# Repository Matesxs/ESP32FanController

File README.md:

# ESP32 PWM Fan Controller

## Description
### This project is still in development so lot of things can be untested or not working at all!

```text
ESP32 10 channel pwm fan controller with control over tcp sockets and serial, 
temperature readout from onewire temperature probes (unlimited count, board have 2 ports), 
fan control routine (automatic - 20 points temperature curves with option of multiple 
temperature inputs and one external temperature value set by control interfaces, manual) 
for 10 separated channels with rpm readout from tacho sensor and led strip control routine with 
predefined effects (some of them use the temperature probes to be able to display temperature).
```

## Features

* 10 Channels for PWM fans
  * Automatic or manual fan speed control
  * Automatic control with 20 point curves with option for multi source temperature input for each fan
* 2 Channels for one wire temperature probes
* 2 Channels for RGB adressable led strips
  * Predefined effects and some even reacts to temperature
  * Support for both 5V and 12V warriants
* Integration for Argus Monitor
* Power by molex or barrel jack (selectable by jumper when stepdown is present)

## Todo

- [x] Publish Schematics for board
- [x] Rework fan control
- [ ] Rework led control

## References

[ESP32 Docs](https://docs.espressif.com/projects/esp-idf/en/latest/esp32/) \
[PlatformIO](https://platformio.org) \
[NeoPixelBus](https://github.com/Makuna/NeoPixelBus) \
[Argus Monitor](https://www.argusmonitor.com) \
[Argus Monitor Controller example](https://github.com/openfancontrol/arguscontroller) \
[DallasTemperature](https://github.com/milesburton/Arduino-Temperature-Control-Library) \
[ArduinoJson](https://github.com/bblanchon/ArduinoJson)

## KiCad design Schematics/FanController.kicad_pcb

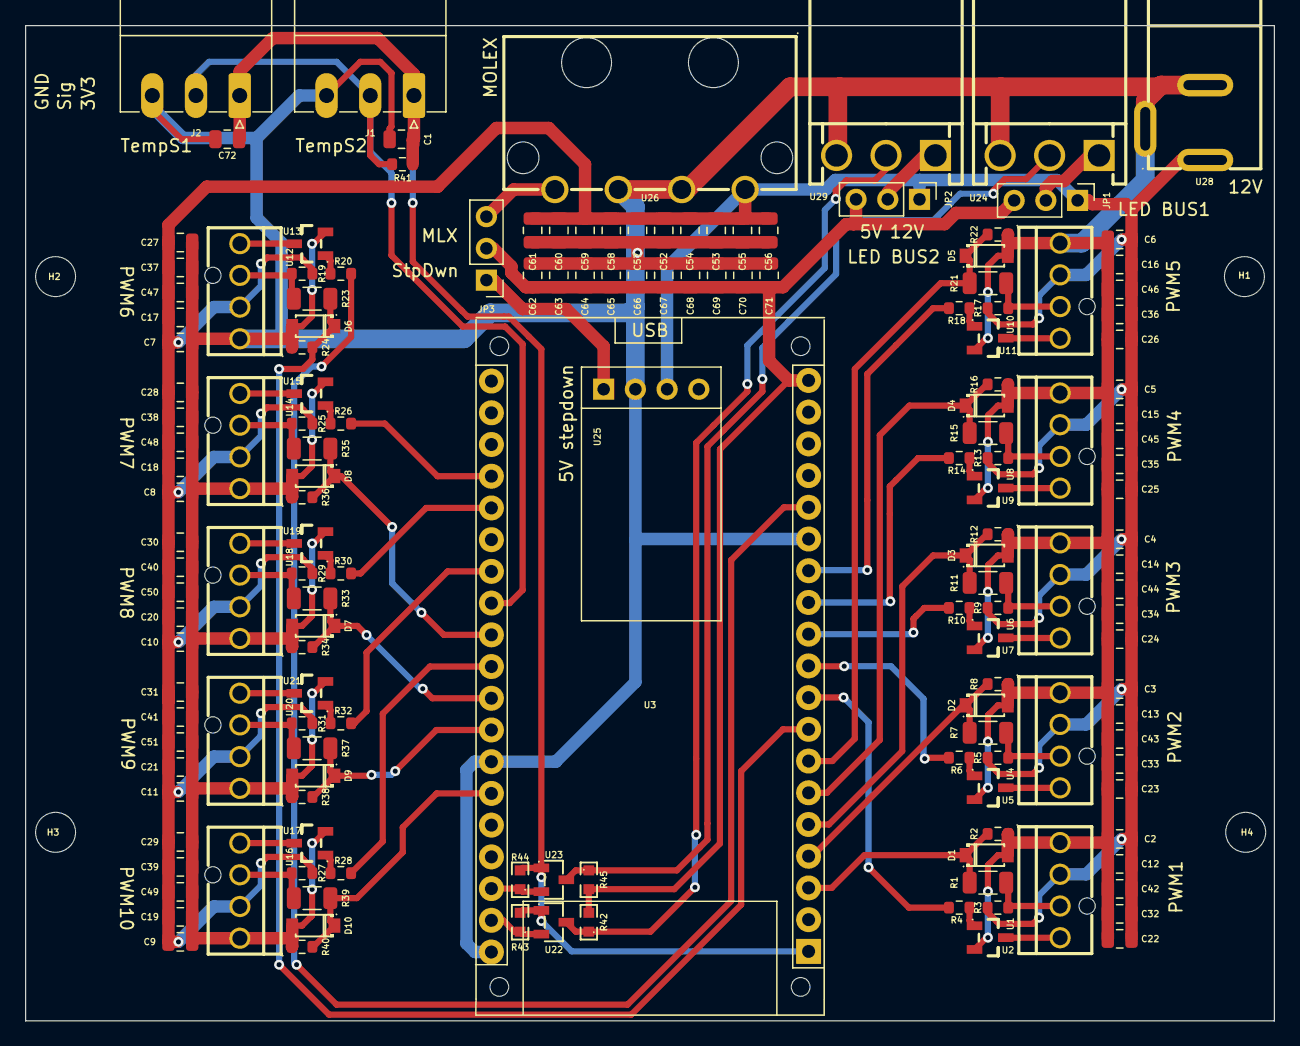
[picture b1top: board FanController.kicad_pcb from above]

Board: 2 copper layers, 100.0 x 79.7 mm, 164 parts (0 on the bottom side), 63 nets.

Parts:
C1, C2, C3, C4, C5, C6, C7, C8, C9, C10, C11, C12, C13, C14, C15, C16, C17, C18, C19, C20, C21, C22, C23, C24, C25, C26, C27, C28, C29, C30, C31, C32, C33, C34, C35, C36, C37, C38, C39, C40, C41, C42, C43, C44, C45, C46, C47, C48, C49, C50, C51, C52, C53, C54, C55, C56, C57, C58, C59, C60, C61, C62, C63, C64, C65, C66, C67, C68, C69, C70, C71, C72: 10u; C_0805_2012Metric
D1, D2, D3, D4, D5, D6, D7, D8, D9, D10: BZT52C3V3; SOD-123_L2.8-W1.8-LS3.7-RD
H1, H2, H3, H4: MountingHole; MountingHole_3.2mm_M3_DIN965
J1: TempSensor1; PhoenixContact_MC_1,5_3-G-3.5_1x03_P3.50mm_Horizontal
J2: TempSensor2; PhoenixContact_MC_1,5_3-G-3.5_1x03_P3.50mm_Horizontal
JP1, JP2: Jumper_3_Open; PinHeader_1x03_P2.54mm_Vertical
JP3: 5V selector; PinHeader_1x03_P2.54mm_Vertical
R1, R7, R11, R15, R21, R23, R33, R35, R37, R39: 2k2; R_1206_3216Metric
R2, R3, R4, R5, R6, R8, R9, R10, R12, R13, R14, R16, R17, R18, R19, R20, R22, R24, R25, R26, R27, R28, R29, R30, R31, R32, R34, R36, R38, R40, R41: 3k3; R_0603_1608Metric
R42, R43, R44, R45: 0603WAF8201T5E; R0603
U1, U4, U6, U8, U10, U12, U14, U16, U18, U20: Fan1; CONN-TH_47053-1000
U2, U5, U7, U9, U11, U13, U15, U17, U19, U21: BC847B,215; SOT-23-3_L2.9-W1.6-P1.90-LS2.8-TL
U3: ES32-DevKitC; MODULE_ESP32-DEVKITC-32D
U22, U23: BSS138; SOT-23-3_L2.9-W1.3-P1.90-LS2.4-BR
U24, U29: S3P-VH(LF)(SN); CONN-TH_3P-P3.96_S3P-VH-LF-SN
U25: STPDWN3V3; ESP32_STPDWN5V
U26: M5082RK-04P; CONN-TH_M5082RK-04P
U28: DC-005_5_5-2_0MM; DC-IN-TH_DC-5520-1

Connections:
+3V3: C1.1, C72.1, J1.1, J2.1, R41.1, R43.2, R44.2, U3.1 (3V3), U22.1 (G), U23.1 (G)
+5V: C62.1, C63.1, C64.1, C65.1, C66.1, C67.1, C68.1, C69.1, C70.1, C71.1, JP1.3 (B), JP2.3 (B), JP3.2 (C), R42.2, R45.2, U3.19 (5V)
+12V: C2.1, C3.1, C4.1, C5.1, C6.1, C7.1, C8.1, C9.1, C10.1, C11.1, C12.1, C13.1, C14.1, C15.1, C16.1, C17.1, C18.1, C19.1, C20.1, C21.1, C22.1, C23.1, C24.1, C25.1, C26.1, C27.1, C28.1, C29.1, C30.1, C31.1, C32.1, C33.1, C34.1, C35.1, C36.1, C37.1, C38.1, C39.1, C40.1, C41.1, C42.1, C43.1, C44.1, C45.1, C46.1, C47.1, C48.1, C49.1, C50.1, C51.1, C52.1, C53.1, C54.1, C55.1, C56.1, C57.1, C58.1, C59.1, C60.1, C61.1, JP1.1 (A), JP2.1 (A), R3.1, R5.1, R9.1, R13.1, R17.1, R19.1, R25.1, R27.1, R29.1, R31.1, U1.2, U4.2, U6.2, U8.2, U10.2, U12.2, U14.2, U16.2, U18.2, U20.2, U25.3 (VIN), U26.1, U28.4
/FAN_Interface1/DI_Tach/IN: R5.2, R7.1, U4.3
/FAN_Interface1/PWM: R6.2, U3.10 (IO26)
/FAN_Interface1/TACH: D2.1 (K), R7.2, R8.1, U3.4 (SVN)
/FAN_Interface2/DI_Tach/IN: R9.2, R11.1, U6.3
/FAN_Interface2/PWM: R10.2, U3.11 (IO27)
/FAN_Interface2/TACH: D3.1 (K), R11.2, R12.1, U3.5 (IO34)
/FAN_Interface3/DI_Tach/IN: R13.2, R15.1, U8.3
/FAN_Interface3/PWM: R14.2, U3.12 (IO14)
/FAN_Interface3/TACH: D4.1 (K), R15.2, R16.1, U3.6 (IO35)
/FAN_Interface4/DI_Tach/IN: R17.2, R21.1, U10.3
/FAN_Interface4/PWM: R18.2, U3.13 (IO12)
/FAN_Interface4/TACH: D5.1 (K), R21.2, R22.1, U3.7 (IO32)
/FAN_Interface5/DI_Tach/IN: R19.2, R23.1, U12.3
/FAN_Interface5/PWM: R20.2, U3.15 (IO13)
/FAN_Interface5/TACH: D6.1 (K), R23.2, R24.1, U3.8 (IO33)
/FAN_Interface6/DI_Tach/IN: R25.2, R35.1, U14.3
/FAN_Interface6/PWM: R26.2, U3.23 (IO15)
/FAN_Interface6/TACH: D8.1 (K), R35.2, R36.1, U3.28 (IO17)
/FAN_Interface7/DI_Tach/IN: R29.2, R33.1, U18.3
/FAN_Interface7/PWM: R30.2, U3.24 (IO2)
/FAN_Interface7/TACH: D7.1 (K), R33.2, R34.1, U3.30 (IO18)
/FAN_Interface8/DI_Tach/IN: R31.2, R37.1, U20.3
/FAN_Interface8/PWM: R32.2, U3.26 (IO4)
/FAN_Interface8/TACH: D9.1 (K), R37.2, R38.1, U3.31 (IO19)
/FAN_Interface9/DI_Tach/IN: R27.2, R39.1, U16.3
/FAN_Interface9/PWM: R28.2, U3.29 (IO5)
/FAN_Interface9/TACH: D10.1 (K), R39.2, R40.1, U3.33 (IO21)
/FAN_Interface/DI_Tach/IN: R1.1, R3.2, U1.3
/FAN_Interface/PWM: R4.2, U3.9 (IO25)
/FAN_Interface/TACH: D1.1 (K), R1.2, R2.1, U3.3 (SVP)
GND: C1.2, C2.2, C3.2, C4.2, C5.2, C6.2, C7.2, C8.2, C9.2, C10.2, C11.2, C12.2, C13.2, C14.2, C15.2, C16.2, C17.2, C18.2, C19.2, C20.2, C21.2, C22.2, C23.2, C24.2, C25.2, C26.2, C27.2, C28.2, C29.2, C30.2, C31.2, C32.2, C33.2, C34.2, C35.2, C36.2, C37.2, C38.2, C39.2, C40.2, C41.2, C42.2, C43.2, C44.2, C45.2, C46.2, C47.2, C48.2, C49.2, C50.2, C51.2, C52.2, C53.2, C54.2, C55.2, C56.2, C57.2, C58.2, C59.2, C60.2, C61.2, C62.2, C63.2, C64.2, C65.2, C66.2, C67.2, C68.2, C69.2, C70.2, C71.2, C72.2, D1.2 (A), D2.2 (A), D3.2 (A), D4.2 (A), D5.2 (A), D6.2 (A), D7.2 (A), D8.2 (A), D9.2 (A), D10.2 (A), J1.3, J2.3, R2.2, R8.2, R12.2, R16.2, R22.2, R24.2, R34.2, R36.2, R38.2, R40.2, U1.1, U2.2, U3.14 (GND), U3.32 (GND), U3.38 (GND), U4.1, U5.2, U6.1, U7.2, U8.1, U9.2, U10.1, U11.2, U12.1, U13.2, U14.1, U15.2, U16.1, U17.2, U18.1, U19.2, U20.1, U21.2, U24.3, U25.2 (GND), U26.2, U26.3, U28.2, U28.3, U29.3
unnamed: J1.2, J2.2, R41.2, U3.27 (IO16)
unnamed: JP1.2 (C), U24.1
unnamed: JP2.2 (C), U29.1
unnamed: JP3.1 (A), U25.1 (VO+)
unnamed: JP3.3 (B), U26.4
unnamed: R4.1, U2.1
unnamed: R6.1, U5.1
unnamed: R10.1, U7.1
unnamed: R14.1, U9.1
unnamed: R18.1, U11.1
unnamed: R20.1, U13.1
unnamed: R26.1, U15.1
unnamed: R28.1, U17.1
unnamed: R30.1, U19.1
unnamed: R32.1, U21.1
unnamed: U1.4, U2.3
unnamed: U4.4, U5.3
unnamed: U6.4, U7.3
unnamed: U8.4, U9.3
unnamed: U10.4, U11.3
unnamed: U12.4, U13.3
unnamed: U14.4, U15.3
unnamed: U16.4, U17.3
unnamed: U18.4, U19.3
unnamed: U20.4, U21.3
unnamed: R42.1, U22.3 (D), U29.2
unnamed: R43.1, U3.37 (IO23), U22.2 (S)
unnamed: R45.1, U23.3 (D), U24.2
unnamed: R44.1, U3.36 (IO22), U23.2 (S)

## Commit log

2023-04-23 init
2023-05-02 refactoring
2023-05-03 fixes
2023-11-01 Added schematics
2025-09-01 preparations for automatic deploy
2025-09-01 Added automatic build pipeline
2025-09-01 updated gitignore
2025-09-01 deleted whole project
2025-09-01 Refactoring/fan control
2025-09-01 minor tweaks
2025-09-04 Update .gitlab-ci.yml file
2025-10-14 upgraded merge script
